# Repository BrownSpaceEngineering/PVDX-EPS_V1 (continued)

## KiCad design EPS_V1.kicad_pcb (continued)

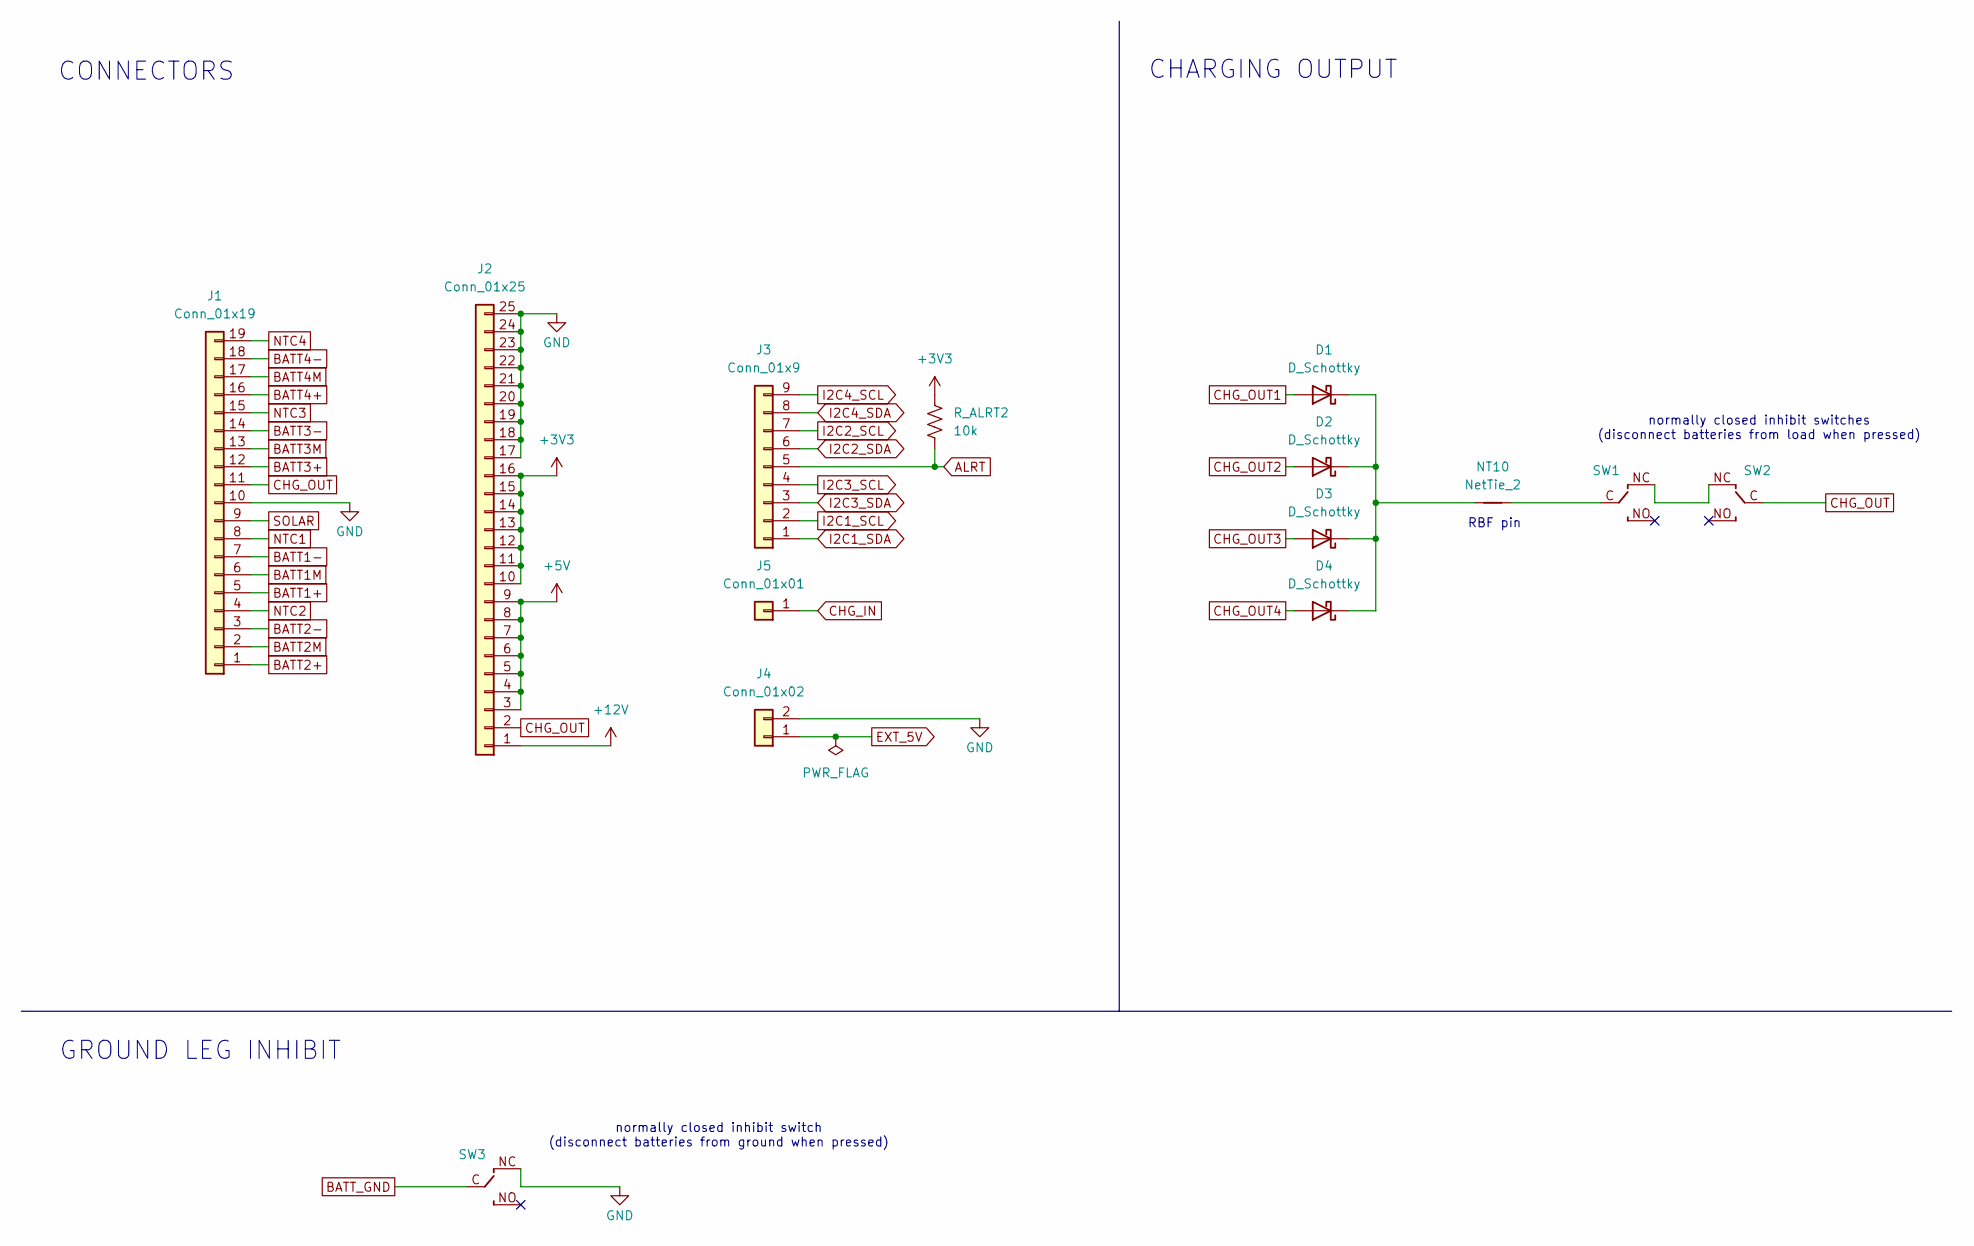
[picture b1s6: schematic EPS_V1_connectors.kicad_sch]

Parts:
D1, D2, D3, D4: D_Schottky; D_SOD-128; MPN RSX301LAM30TR
J1: Conn_01x19; PinHeader_1x19_P2.54mm_Vertical
J2: Conn_01x25; PinHeader_1x25_P2.54mm_Vertical
J3: Conn_01x9; PinHeader_1x09_P2.54mm_Vertical
J4: Conn_01x02; PinHeader_1x02_P2.54mm_Vertical
J5: Conn_01x01; PinHeader_1x01_P2.54mm_Vertical
NT10: NetTie_2; RBF
R_ALRT2: 10k; R_0603_1608Metric
SW1, SW3: SWITCH; SWITCH-R
SW2: SWITCH; SWITCH-L

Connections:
+3V3: J2.10, J2.11, J2.12, J2.13, J2.14, J2.15, J2.16, R_ALRT2.1; also elsewhere on the board
+5V: J2.3, J2.4, J2.5, J2.6, J2.7, J2.8, J2.9; also elsewhere on the board
+12V: J2.1; also elsewhere on the board
ALRT: J3.5, R_ALRT2.2; also elsewhere on the board
BATT1+: J1.5; also elsewhere on the board
BATT1-: J1.7; also elsewhere on the board
BATT1M: J1.6; also elsewhere on the board
BATT2+: J1.1; also elsewhere on the board
BATT2-: J1.3; also elsewhere on the board
BATT2M: J1.2; also elsewhere on the board
BATT3+: J1.12; also elsewhere on the board
BATT3-: J1.14; also elsewhere on the board
BATT3M: J1.13; also elsewhere on the board
BATT4+: J1.16; also elsewhere on the board
BATT4-: J1.18; also elsewhere on the board
BATT4M: J1.17; also elsewhere on the board
BATT_GND: SW3.C (COM); also elsewhere on the board
CHG_IN: J5.1 (Pin_1_1); also elsewhere on the board
CHG_OUT: J1.11, J2.2, SW2.C (COM); also elsewhere on the board
CHG_OUT1: D1.2 (A); also elsewhere on the board
CHG_OUT2: D2.2 (A); also elsewhere on the board
CHG_OUT3: D3.2 (A); also elsewhere on the board
CHG_OUT4: D4.2 (A); also elsewhere on the board
EXT_5V: J4.1; also elsewhere on the board
GND: J1.10, J2.17, J2.18, J2.19, J2.20, J2.21, J2.22, J2.23, J2.24, J2.25, J4.2, SW3.NC; also elsewhere on the board
I2C1_SCL: J3.2; also elsewhere on the board
I2C1_SDA: J3.1; also elsewhere on the board
I2C2_SCL: J3.7; also elsewhere on the board
I2C2_SDA: J3.6; also elsewhere on the board
I2C3_SCL: J3.4; also elsewhere on the board
I2C3_SDA: J3.3; also elsewhere on the board
I2C4_SCL: J3.9; also elsewhere on the board
I2C4_SDA: J3.8; also elsewhere on the board
NTC1: J1.8; also elsewhere on the board
NTC2: J1.4; also elsewhere on the board
NTC3: J1.15; also elsewhere on the board
NTC4: J1.19; also elsewhere on the board
unnamed: D1.1 (K), D2.1 (K), D3.1 (K), D4.1 (K), NT10.1
unnamed: NT10.2, SW1.C (COM)
unnamed: SW1.NC, SW2.NC
SOLAR: J1.9; also elsewhere on the board

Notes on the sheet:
CONNECTORS
RBF pin
normally closed inhibit switch (disconnect batteries from ground when pressed)
GROUND LEG INHIBIT
normally closed inhibit switches (disconnect batteries from load when pressed)
CHARGING OUTPUT

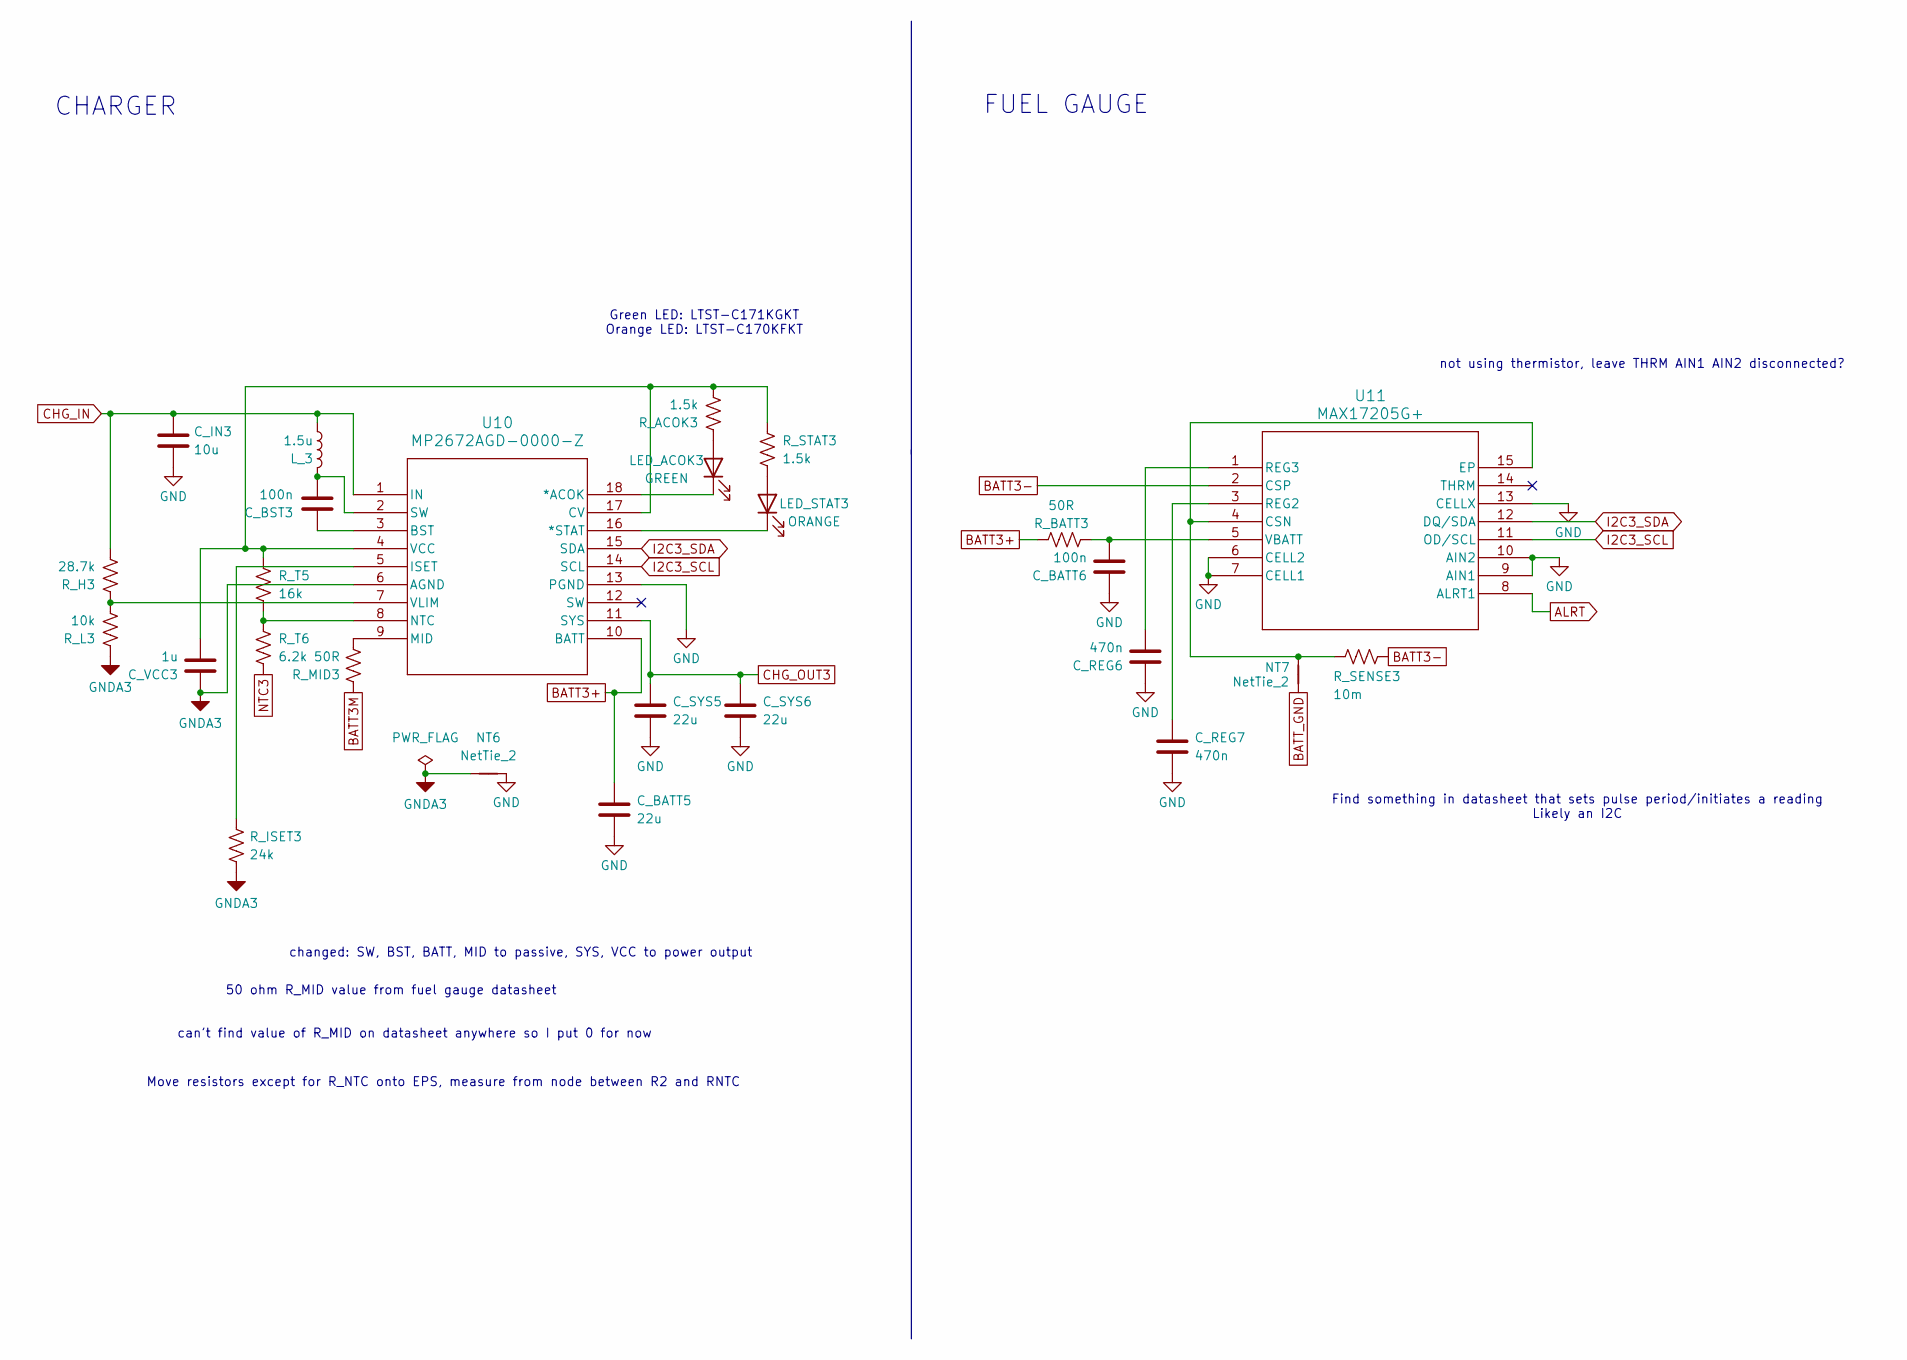
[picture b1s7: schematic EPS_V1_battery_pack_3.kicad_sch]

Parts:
C_BATT5: 22u; C_0805_2012Metric; Voltage Rating 25V
C_BATT6: 100n; C_0603_1608Metric; Voltage Rating 16V
C_BST3: 100n; C_0603_1608Metric; Voltage Rating 16V
C_IN3: 10u; C_0805_2012Metric; Voltage Rating 25V
C_REG6, C_REG7: 470n; C_0603_1608Metric; Voltage Rating 16V
C_SYS5, C_SYS6: 22u; C_0805_2012Metric; Voltage Rating 25V
C_VCC3: 1u; C_0603_1608Metric; Voltage Rating 16V
LED_ACOK3: GREEN; LED_0805_2012Metric; MPN LTST-C171KGKT
LED_STAT3: ORANGE; LED_0805_2012Metric; MPN LTST-C170KFKT
L_3: 1.5u; IND_AMELA2012S-1R5MT; MPN AMELA2012S-1R5MT
NT6, NT7: NetTie_2; NetTie-2_SMD_Pad0.5mm
R_ACOK3: 1.5k; R_0603_1608Metric
R_BATT3: 50R; R_0603_1608Metric
R_H3: 28.7k; R_0603_1608Metric
R_ISET3: 24k; R_0603_1608Metric
R_L3: 10k; R_0603_1608Metric
R_MID3: 50R; R_0603_1608Metric
R_SENSE3: 10m; R_0603_1608Metric
R_STAT3: 1.5k; R_0603_1608Metric
R_T5: 16k; R_0603_1608Metric
R_T6: 6.2k; R_0603_1608Metric
U10: MP2672AGD-0000-Z; QFN-18_MP2672A_MNP
U11: MAX17205G+; 21-0137_T1433&plus_2C_MXM

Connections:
ALRT: U11.8 (ALRT1); also elsewhere on the board
BATT3+: C_BATT5.1, R_BATT3.1, U10.10 (BATT); also elsewhere on the board
BATT3-: R_SENSE3.1, U11.2 (CSP); also elsewhere on the board
BATT3M: R_MID3.1; also elsewhere on the board
BATT_GND: NT7.1; also elsewhere on the board
CHG_IN: C_IN3.1, L_3.1, R_H3.2, U10.1 (IN); also elsewhere on the board
CHG_OUT3: C_SYS5.1, C_SYS6.1, U10.11 (SYS); also elsewhere on the board
GND: C_BATT5.2, C_BATT6.1, C_IN3.2, C_REG6.1, C_REG7.2, C_SYS5.2, C_SYS6.2, NT6.2, U10.13 (PGND), U11.6 (CELL2), U11.7 (CELL1), U11.9 (AIN1), U11.10 (AIN2), U11.13 (CELLX); also elsewhere on the board
GNDA3: C_VCC3.1, NT6.1, R_ISET3.2, R_L3.1, U10.6 (AGND)
I2C3_SCL: U10.14 (SCL), U11.11 (OD/SCL); also elsewhere on the board
I2C3_SDA: U10.15 (SDA), U11.12 (DQ/SDA); also elsewhere on the board
NTC3: R_T6.2; also elsewhere on the board
unnamed: C_BST3.2, L_3.2, U10.2 (SW)
unnamed: LED_ACOK3.2 (A), R_ACOK3.1
unnamed: LED_ACOK3.1 (K), U10.18 (*ACOK)
unnamed: LED_STAT3.2 (A), R_STAT3.2
unnamed: LED_STAT3.1 (K), U10.16 (*STAT)
unnamed: C_BST3.1, U10.3 (BST)
unnamed: C_VCC3.2, R_ACOK3.2, R_STAT3.1, R_T5.1, U10.4 (VCC), U10.17 (CV)
unnamed: R_ISET3.1, U10.5 (ISET)
unnamed: R_MID3.2, U10.9 (MID)
unnamed: R_T5.2, R_T6.1, U10.8 (NTC)
unnamed: R_H3.1, R_L3.2, U10.7 (VLIM)
unnamed: NT7.2, R_SENSE3.2, U11.4 (CSN), U11.15 (EP)
unnamed: C_REG7.1, U11.3 (REG2)
unnamed: C_REG6.2, U11.1 (REG3)
unnamed: C_BATT6.2, R_BATT3.2, U11.5 (VBATT)

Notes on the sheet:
Move resistors except for R_NTC onto EPS, measure from node between R2 and RNTC
Green LED: LTST-C171KGKT Orange LED: LTST-C170KFKT
can't find value of R_MID on datasheet anywhere so I put 0 for now
FUEL GAUGE
CHARGER
changed: SW, BST, BATT, MID to passive, SYS, VCC to power output
50 ohm R_MID value from fuel gauge datasheet
not using thermistor, leave THRM AIN1 AIN2 disconnected?
Find something in datasheet that sets pulse period/initiates a reading Likely an I2C

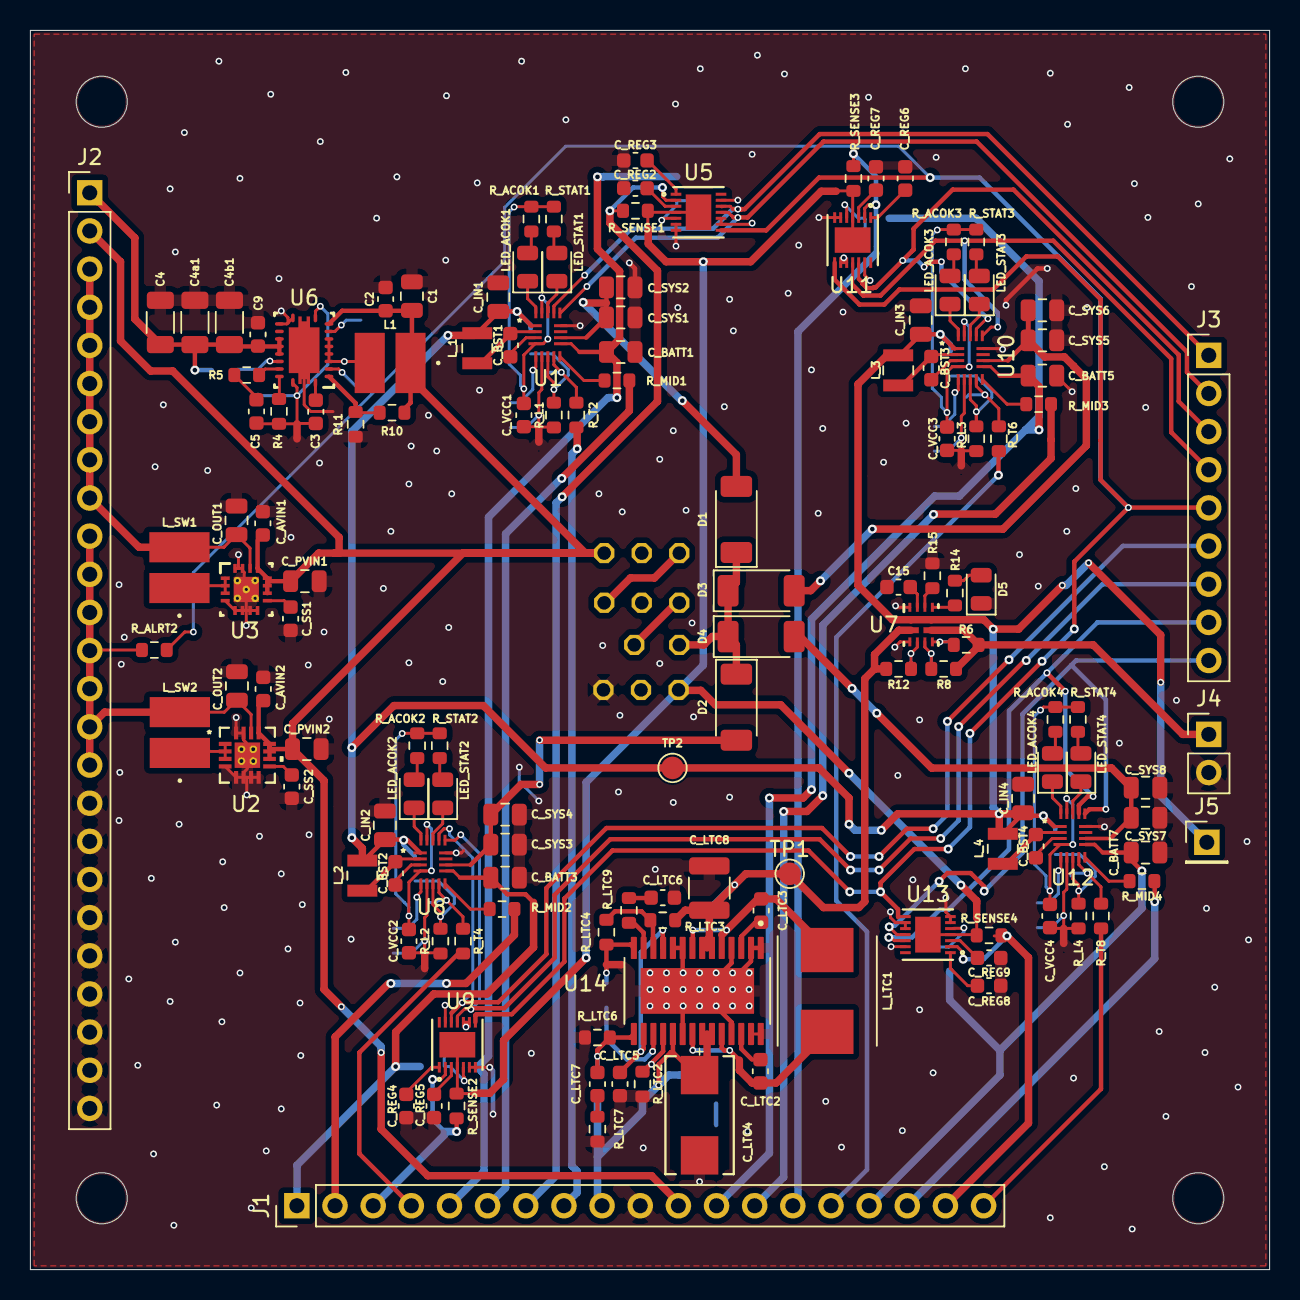
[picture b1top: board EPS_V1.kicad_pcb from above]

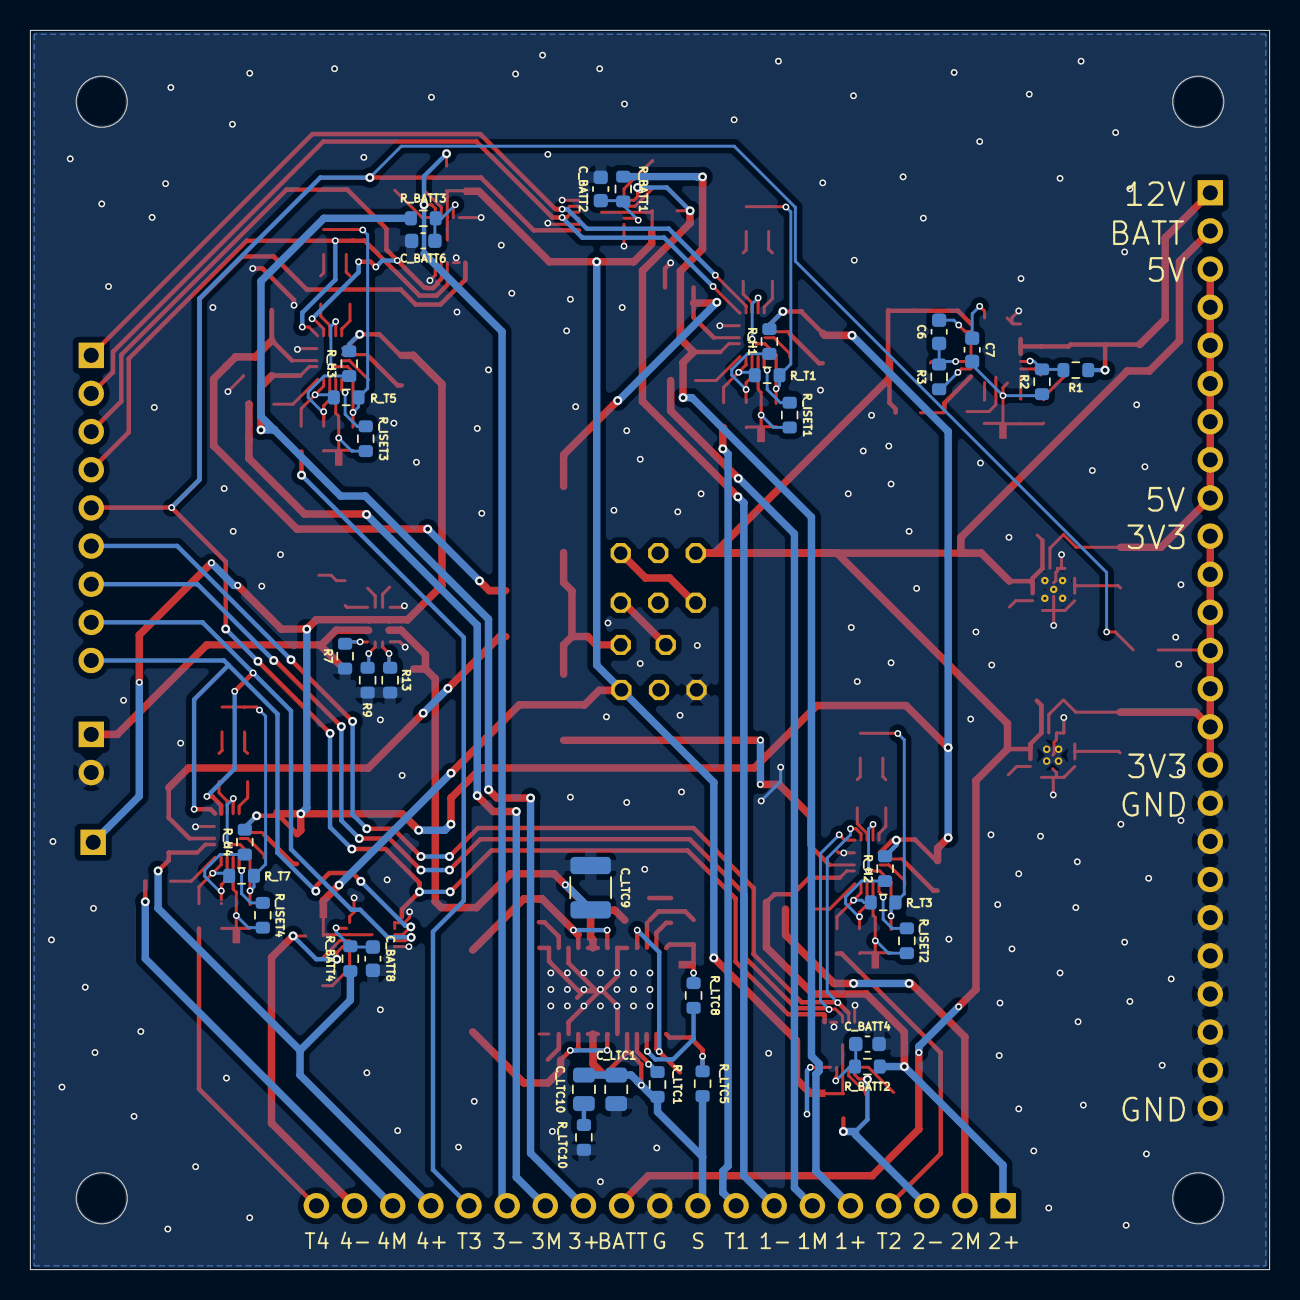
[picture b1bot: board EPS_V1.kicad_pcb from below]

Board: 2 copper layers, 82.5 x 82.5 mm, 186 parts (35 on the bottom side), 142 nets.

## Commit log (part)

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2026-04-18 Add connectors, 5V & 3V3 buck converters, 1 battery pack & charger
2026-04-18 Minor fixes
2026-04-21 Add solar to charger buck-boost converter, make charger standalone instead of host control
2026-04-23 Add fuel gauge, fix voltage labels
2026-04-23 Add fuel gauge ALRT lines
2026-04-26 Add boost converter to 12V, fix grounding
2026-04-29 Add 12V boost values
2026-04-29 Add 5V charging input
2026-04-30 Clarify global net naming, other minor fixes
2026-04-30 Add inhibit switches
2026-05-01 Add all footprints except connectors & switches, change to net ties over 0 ohm resistors
2026-05-01 Clean up & add labels
2026-05-01 Add notes from Harvey meeting
2026-05-02 assigned footprints to headers
2026-05-03 Add power switching IC
2026-05-04 Add other battery packs, connect all ALRT signals, assign footprints for new components, make inhibit switch footprints
2026-05-04 Change new resistors to standard values
2026-05-04 Added Spice sims, models, translator python module for TI -> LT model conversion
2026-05-15 Do layout draft
